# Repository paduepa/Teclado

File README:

este es mi proyecto de un pequeño teclado gaming

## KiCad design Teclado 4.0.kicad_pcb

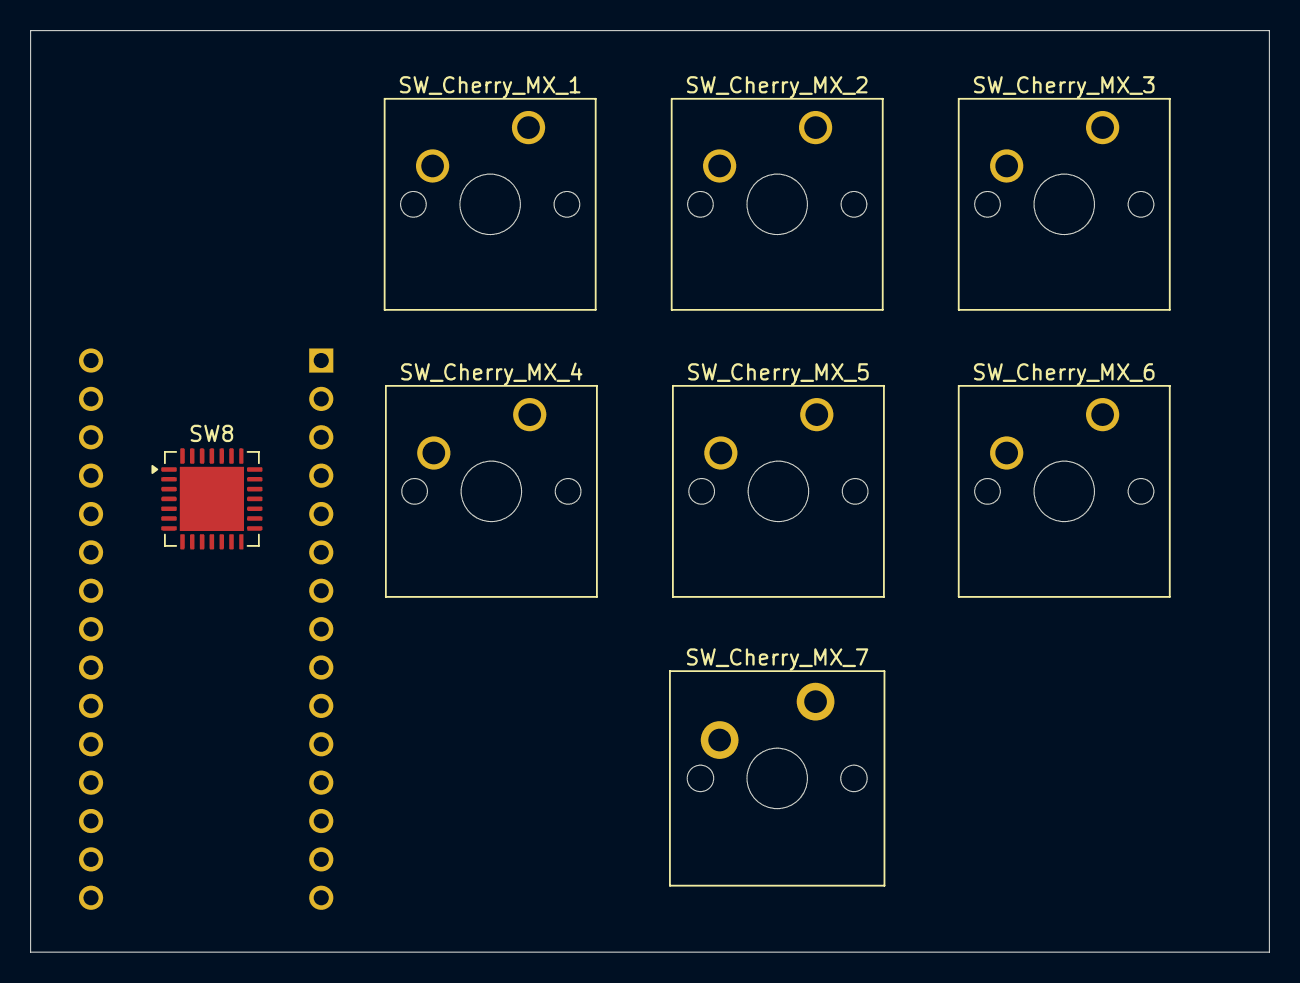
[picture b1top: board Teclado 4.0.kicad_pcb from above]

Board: 2 copper layers, 82.0 x 61.0 mm, 9 parts (1 on the bottom side), 2 nets, no tracks yet.

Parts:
A1: Arduino_Nano_RP2040_Connect; Arduino_Nano
SW8: RotaryEncoder_Switch; QFN-28-1EP_6x6mm_P0.65mm_EP4.25x4.25mm
SW_Cherry_MX_1, SW_Cherry_MX_2, SW_Cherry_MX_3, SW_Cherry_MX_4, SW_Cherry_MX_5, SW_Cherry_MX_6: SW_Cherry_MX_1.00u_PCB
SW_Cherry_MX_7: SW_Cherry_MX_PCB_3.00u

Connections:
/COL0: A1.7 (D4), A1.8 (D5)
unnamed: A1.4 (GND), A1.29 (GND)
